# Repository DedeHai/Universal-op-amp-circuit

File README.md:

# Universal-op-amp-circuit
PCB design for SO8 dual op-amp and SOT23-5 single op-amp 

more details and ordering information on my blog: https://bashtelorofscience.wordpress.com/2017/06/05/universal-op-amp-circuit-pcb/

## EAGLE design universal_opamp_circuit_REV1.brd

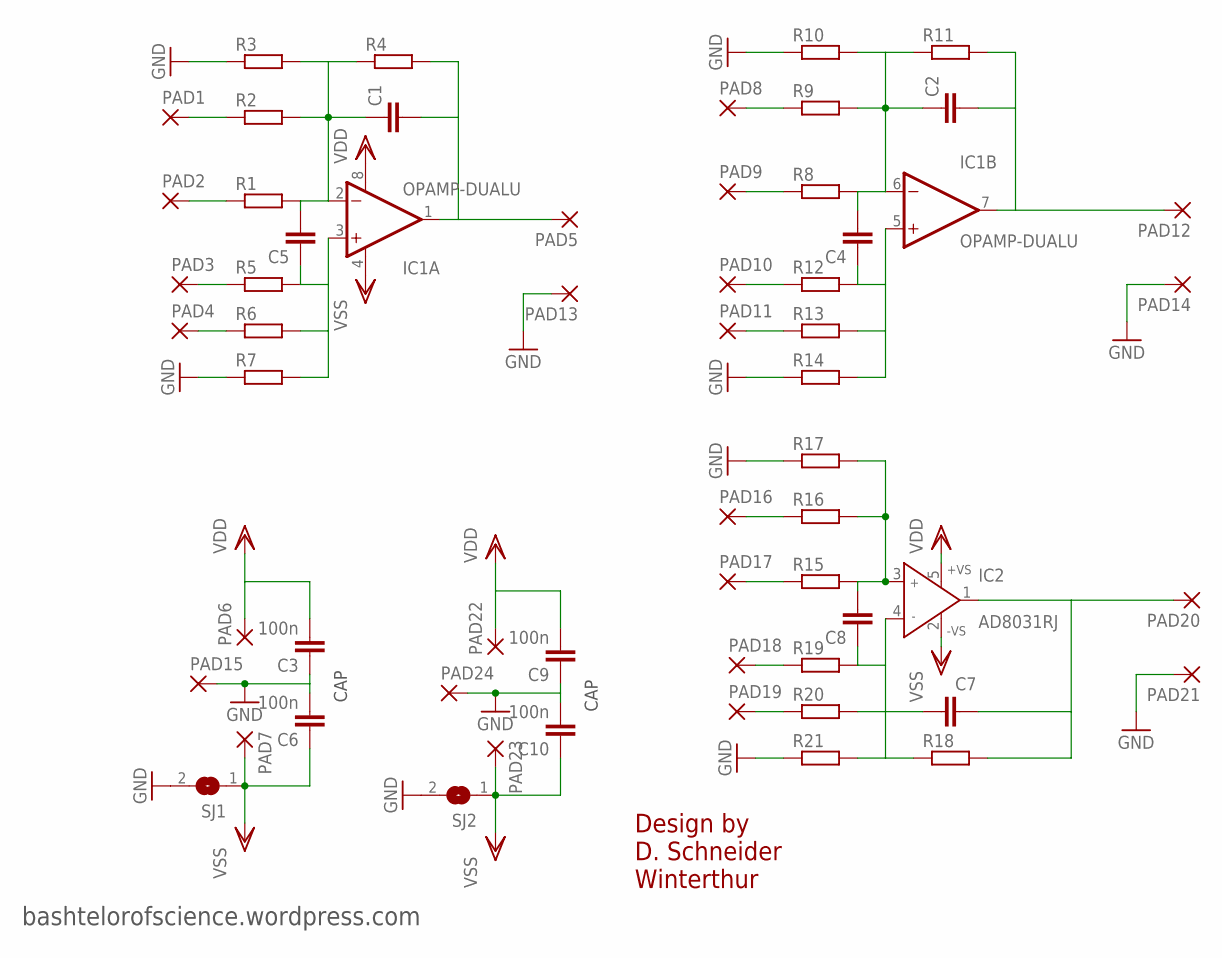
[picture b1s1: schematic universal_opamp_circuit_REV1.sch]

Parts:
C1, C2, C4, C5, C7, C8: C-EUC0603; C0603
C3, C6, C9, C10: 100n; C0603
IC1: OPAMP-DUALU; SO08
IC2: AD8031RJ; SOT23-5
PAD1, PAD2, PAD3, PAD4, PAD5, PAD6, PAD7, PAD8, PAD9, PAD10, PAD11, PAD12, PAD13, PAD14, PAD15, PAD16, PAD17, PAD18, PAD19, PAD20, PAD21, PAD22, PAD23, PAD24: 1,6/0,9
R1, R2, R3, R4, R5, R6, R7, R8, R9, R10, R11, R12, R13, R14, R15, R16, R17, R18, R19, R20, R21: R-EU_R0603; R0603
SJ1, SJ2: SJ

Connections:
GND: C3.1, C6.2, C9.1, C10.2, PAD13.1, PAD14.1, PAD15.1, PAD21.1, PAD24.1, R3.1, R7.1, R10.1, R14.1, R17.1, R21.1, SJ1.2, SJ2.2
unnamed: C2.1, C4.2, IC1.6 (-IN), R8.2, R9.2, R10.2, R11.1
unnamed: C2.2, IC1.7 (OUT), PAD12.1, R11.2
unnamed: PAD1.1, R2.1
unnamed: C4.1, IC1.5 (+IN), R12.2, R13.2, R14.2
unnamed: C5.1, IC1.3 (+IN), R5.2, R6.2, R7.2
unnamed: PAD2.1, R1.1
unnamed: PAD3.1, R5.1
unnamed: PAD4.1, R6.1
unnamed: PAD8.1, R9.1
unnamed: PAD11.1, R13.1
unnamed: C8.2, IC2.3 (IN+), R15.2, R16.2, R17.2
unnamed: C7.2, IC2.1 (OUT), PAD20.1, R18.2
unnamed: C1.1, C5.2, IC1.2 (-IN), R1.2, R2.2, R3.2, R4.1
unnamed: C1.2, IC1.1 (OUT), PAD5.1, R4.2
unnamed: PAD9.1, R8.1
unnamed: PAD10.1, R12.1
unnamed: C7.1, C8.1, IC2.4 (IN-), R18.1, R19.2, R20.2, R21.2
unnamed: PAD16.1, R16.1
unnamed: PAD17.1, R15.1
unnamed: PAD18.1, R19.1
unnamed: PAD19.1, R20.1
VDD: C3.2, C9.2, IC1.8 (V+), IC2.5 (+VS), PAD6.1, PAD22.1
VSS: C6.1, C10.1, IC1.4 (V-), IC2.2 (-VS), PAD7.1, PAD23.1, SJ1.1, SJ2.1

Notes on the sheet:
CAP
Design by D. Schneider Winterthur
bashtelorofscience.wordpress.com

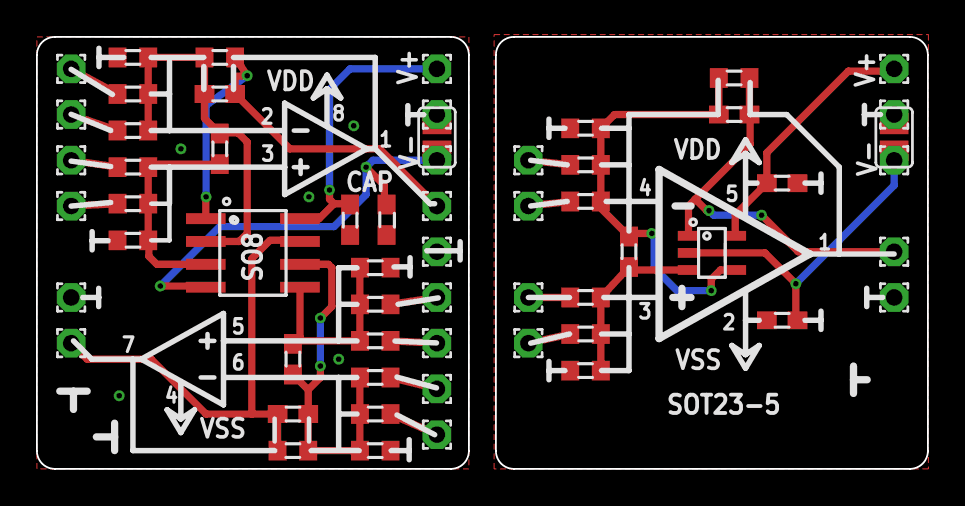
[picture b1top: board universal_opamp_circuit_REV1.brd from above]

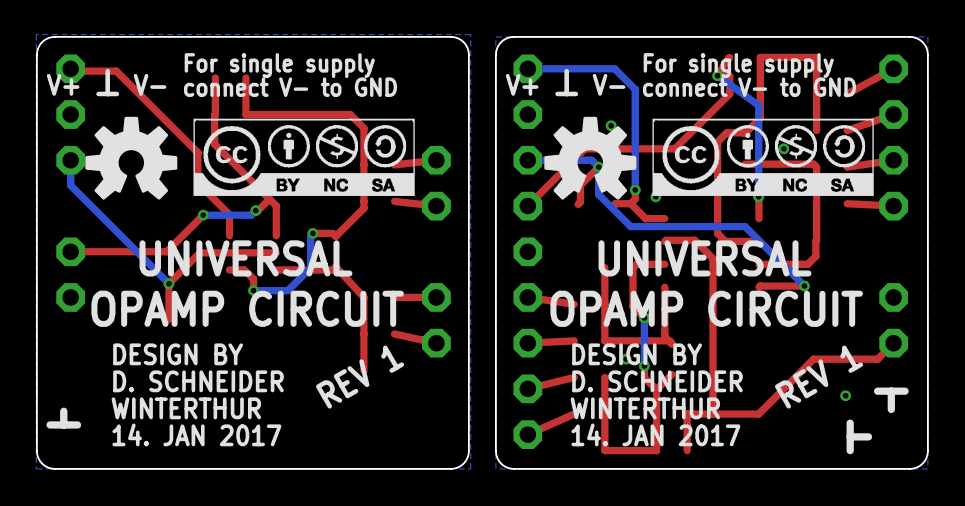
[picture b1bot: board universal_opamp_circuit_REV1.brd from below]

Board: 2 copper layers, 49.5 x 24.0 mm, 63 parts (4 on the bottom side), 24 nets.

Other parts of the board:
U$1, U$4: CC-BY-NC-SA
U$2, U$3: OSHW-LOGO-M

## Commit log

2017-06-05 added photos, update schematic info
2017-06-05 photos added
2017-06-05 add photo
2017-06-05 added dots to schematic paths

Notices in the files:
parts and their libraries:
SparkFun-AnalogIC: Licensing:Creative Commons ShareAlike 4.0 International - https://creativecommons.org/licenses/by-sa/4.0
